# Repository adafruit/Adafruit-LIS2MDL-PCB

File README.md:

## Adafruit LIS2MDL 3-Axis Magnetometer PCB

<a href="http://www.adafruit.com/products/4488"><br/>
Click here to purchase one from the Adafruit shop</a>

PCB files for the Adafruit LIS2MDL 3-Axis Magnetometer. 

Format is EagleCAD schematic and board layout
* https://www.adafruit.com/product/4488

### Description

Sense the magnetic fields that surround us with this handy triple-axis magnetometer (compass) module. Magnetometers can sense where the strongest magnetic force is coming from, generally used to detect magnetic north, but can also be used for measuring magnetic fields. This sensor tends to be paired with a 6-DoF (degree of freedom) accelerometer/gyroscope to create a 9-DoF inertial measurement unit that can detect its orientation in real-space thanks to Earth's stable magnetic field. It's a great match for any of our 6-DoF IMU sensors such as the LSM6DSOX or LSM6DS33.

### License

Adafruit invests time and resources providing this open source design, please support Adafruit and open-source hardware by purchasing products from [Adafruit](https://www.adafruit.com)!

Designed by Limor Fried/Ladyada for Adafruit Industries.

Creative Commons Attribution/Share-Alike, all text above must be included in any redistribution. 
See license.txt for additional details.

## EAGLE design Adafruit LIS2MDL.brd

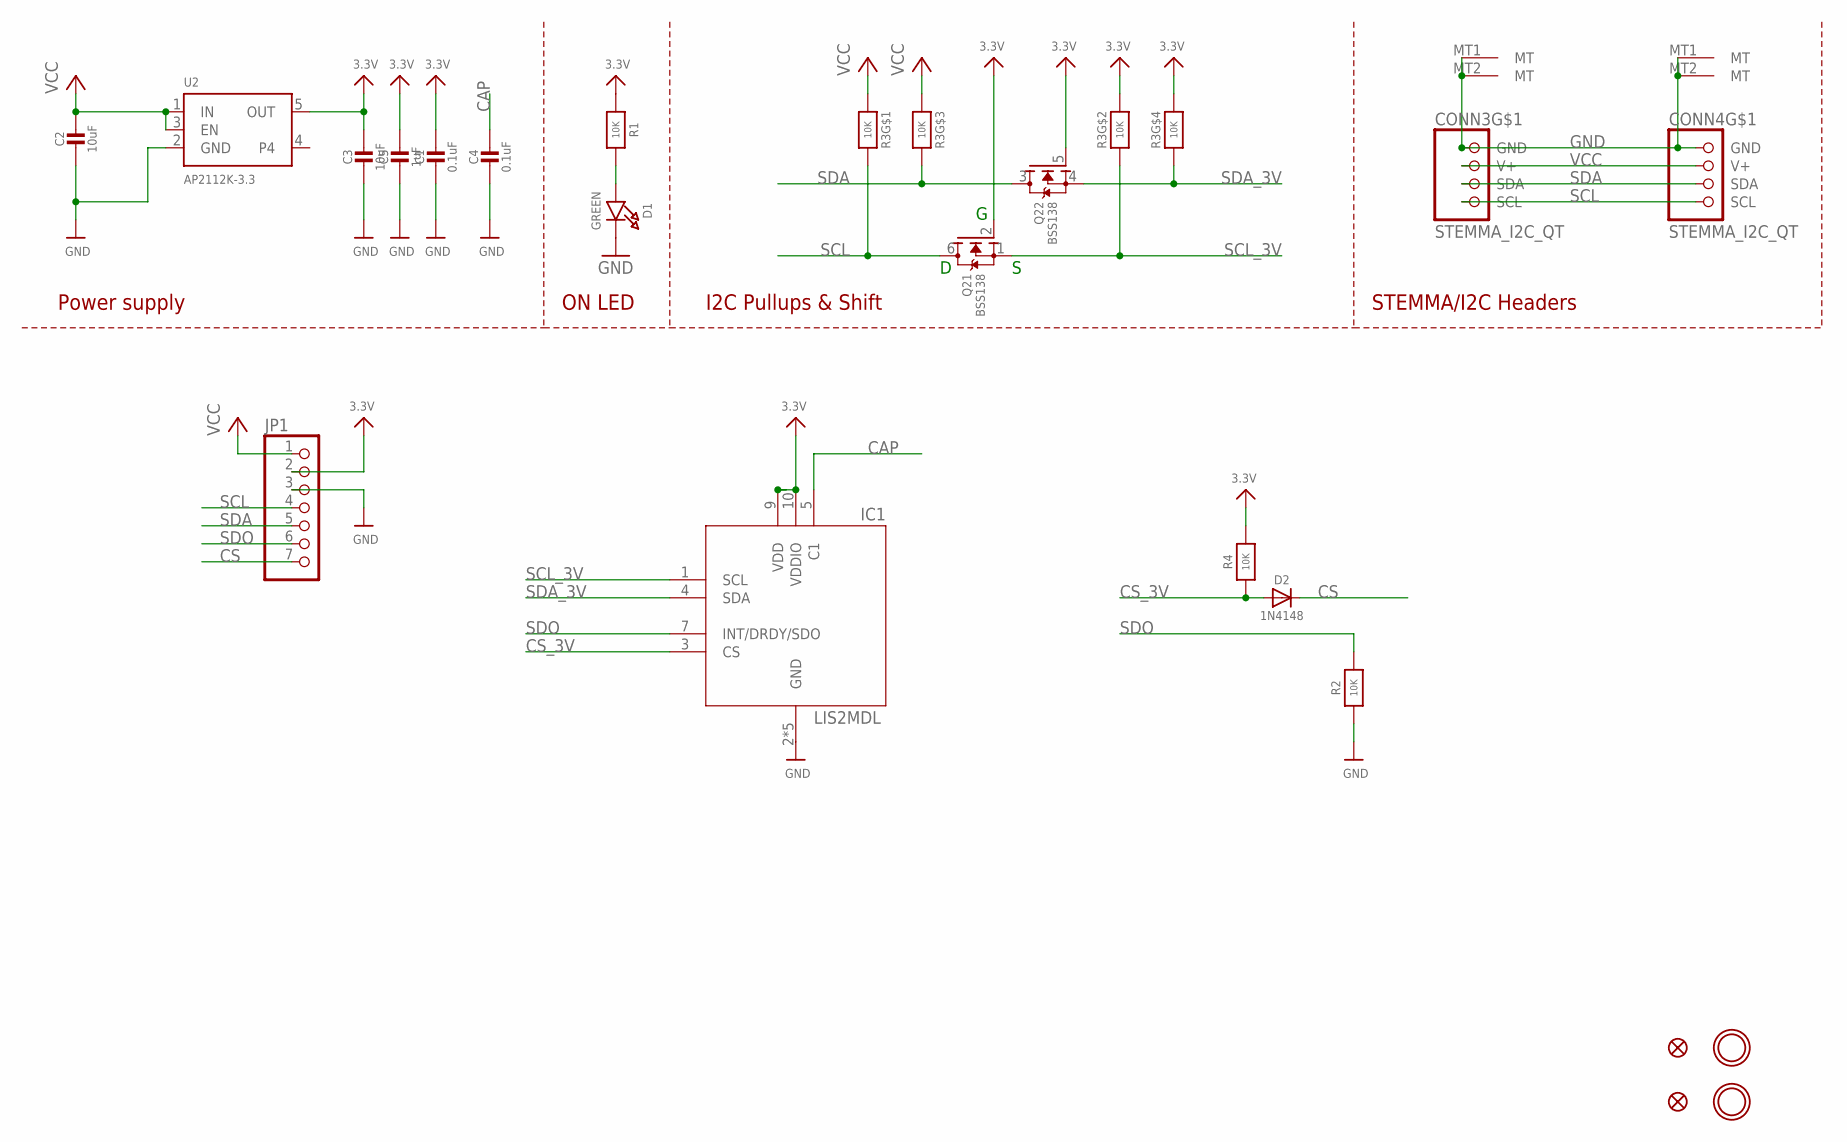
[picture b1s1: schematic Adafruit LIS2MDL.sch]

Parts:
C1, C4: 0.1uF; 0603-NO
C2, C3: 10uF; 0805-NO
C5: 1uF; 0603-NO
CONN3, CONN4: STEMMA_I2C_QT; JST_SH4
D1: GREEN; CHIPLED_0603_NOOUTLINE
D2: 1N4148; SOD-323
FID3, FID4: FIDUCIAL_1MM
IC1: LIS2MDL; LGA12_2X2MM
JP1: HEADER-1X770MIL; 1X07_ROUND_70
Q2: BSS138; SOT363
R1, R2, R4: 10K; 0603-NO
R3: 10K; RESPACK_4X0603
U2: AP2112K-3.3; SOT23-5
U$1, U$17: MOUNTINGHOLE2.5; MOUNTINGHOLE_2.5_PLATED

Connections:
3.3V: C1.1, C3.1, C5.1, IC1.9 (VDD), IC1.10 (VDDIO), JP1.2, Q2.2 (G), Q2.5 (G), R1.1, R3.2 (1), R3.4 (1), R4.2, U2.5 (OUT)
CAP: C4.1, IC1.5 (C1)
CS: D2.C, JP1.7
CS_3V: D2.A, IC1.3 (CS), R4.1
GND: C1.2, C2.2, C3.2, C4.2, C5.2, CONN3.1 (GND), CONN3.MT1 (MT), CONN3.MT2 (MT), CONN4.1 (GND), CONN4.MT1 (MT), CONN4.MT2 (MT), D1.C, IC1.2 (GND), IC1.6 (GND), IC1.8 (GND), IC1.11 (GND), IC1.12 (GND), JP1.3, R2.1, U2.2 (GND)
unnamed: D1.A, R1.2
SCL: CONN3.4 (SCL), CONN4.4 (SCL), JP1.4, Q2.6 (D), R3.8 (2)
SCL_3V: IC1.1 (SCL), Q2.1 (S), R3.7 (2)
SDA: CONN3.3 (SDA), CONN4.3 (SDA), JP1.5, Q2.3 (D), R3.6 (2)
SDA_3V: IC1.4 (SDA), Q2.4 (S), R3.5 (2)
SDO: IC1.7 (INT/DRDY/SDO), JP1.6, R2.2
VCC: C2.1, CONN3.2 (V+), CONN4.2 (V+), JP1.1, R3.1, R3.3 (1), U2.1 (IN), U2.3 (EN)

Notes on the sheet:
I2C Pullups & Shift
STEMMA/I2C Headers
ON LED
Power supply

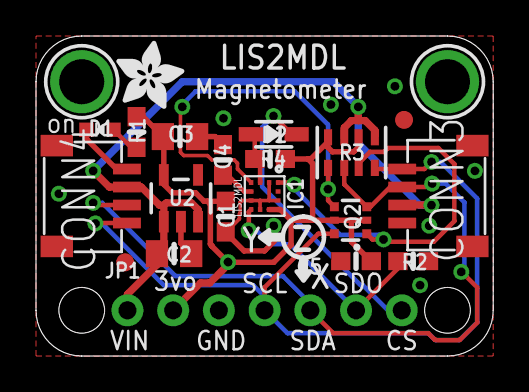
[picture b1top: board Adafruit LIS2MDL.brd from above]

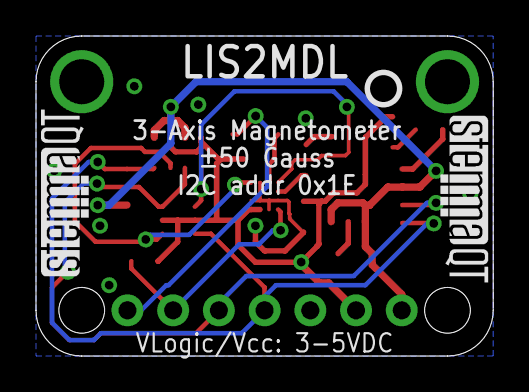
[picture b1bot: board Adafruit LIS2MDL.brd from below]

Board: 2 copper layers, 25.4 x 17.8 mm, 25 parts (3 on the bottom side), 12 nets.

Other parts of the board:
U$11: ADAFRUIT_3.5MM
U$25: PCBFEAT-REV-040
U$30, U$31: STEMMAQT

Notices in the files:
parts and their libraries:
microbuilder: This work is placed in the public domain, and may be freely used for commercial and non-commercial work with the following conditions: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
